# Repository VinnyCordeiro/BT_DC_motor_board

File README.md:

# BoxTurtle DC motors standalone board
A standalone board to control the DC motors of the BoxTurtle.

IMPORTANT NOTE: this design is still untested and being modified frequently as bugs/flaws are found. Do not order PCBs yet until we say it's safe!

## Why
The [AFC-Lite](https://github.com/xbst/AFC-Lite) is the preferred board for the BoxTurtle, but it is quite expensive and is only available on xbst's store (which is fair). However, many of us (myself included) already have a stash of old 3D printer controller boards to take care of the stepper motors, so only the DC motors were left without a standalone solution to control them. This board is an attempt to solve this situation.

I designed the board to be as easy and cheap as possible; with that in mind, here are the design constraints:
- All components/modules must be through hole mounted: I have professional training in electronics and the tools so SMD isn't a problem, but this isn't true for most of the hobbyists; by using through hole components the soldering complexity barrier is lowered;
- All modules are to be mounted on sockets: this opens some space on the board that would be otherwise unavailable. _DO NOT_ solder the modules directly on the board: not only you'll ruin the modularity of the design, you won't be able to install the power selection circuitry on the board (you may get away by soldering wires at the bottom side of the board for the switch, and solder the diodes at the bottom, but that's a bodge and shouldn't be used);
- I added as much useful information on the board silkscreen as I could, with the exception of the pinout. This should help guiding how the components/modules must be mounted, so it's on you if you let the magic smoke out if mounting them the other way around.

## Bill of Materials
This board was made with modularity in mind, so you'll need to buy those modules from Aliexpress (or any other source as long as the footprint matches; if they don't, you'll need to modify the PCB yourself):
|Component|No. Needed|Comment|Sourcing URL|
|---------|----------|-------|-------|
|5.08mm Screw Terminal|1|Power Input|https://www.lcsc.com/product-detail/Screw-span-style-background-color-ff0-terminal-span_MAX-MX129-5-08-02P-GN01-Cu-Y-A_C5188485.html|
|Automotive Mini-Blade Fuse Holder|1|Takes [Mini Automotive Fuses](https://www.keyelco.com/product.cfm/product_id/1376)|https://www.lcsc.com/product-detail/Fuse-Holders_XFCN-XF-506P_C492610.html|
|2A Mini Automotive fuse|1|For circuit safety|https://www.lcsc.com/product-detail/Automotive-Fuses_Littelfuse-0297002-WXNV_C151091.html|
|DC-DC 3A buck converter|1|Pick the 5V version|https://www.aliexpress.com/item/1005007031557776.html|
|LDO 800MA DC 5V to 3.3V buck converter|1|They come with right angle pin headers, you have to swap for straight pins|https://www.aliexpress.com/item/1005007792706354.html|
|DRV8837 2 Way DC H-Bridge|2|Pick the version with 2 drivers on the board|https://www.aliexpress.com/item/1005007587993921.html|
|SN65HVD230 CAN Network Transceiver Board|1|Optional, only if CAN bus will be used. You may need a jumper for the termination resistor if this is at the end of the CAN bus|https://www.aliexpress.com/item/1005006438437964.html|
|Jumper|1|If you doesn't have one|https://www.lcsc.com/product-detail/Shunts-Jumpers_TE-Connectivity-2-881545-2_C5166780.html|
|Pin socket 2 pins|4|For the 5V buck converter module|https://www.lcsc.com/product-detail/Female-Headers_BOOMELE-Boom-Precision-Elec-2-54-1-2P_C49661.html|
|Pin socket 3 pins|1|For the 3.3V buck converter module|https://www.lcsc.com/product-detail/Female-Headers_BOOMELE-Boom-Precision-Elec-2-54-1-3P_C146243.html|
|Pin socket 4 pins|1|For the CAN transceiver module|https://www.lcsc.com/product-detail/Female-Headers_BOOMELE-Boom-Precision-Elec-2-54-1-4P_C2718488.html|
|Pin socket 8 pins|4|For the DRV8837 modules|https://www.lcsc.com/product-detail/Female-Headers_BOOMELE-Boom-Precision-Elec-2-54-1-8P_C27438.html|
|Pin socket 20 pins|2|For the MCU|https://www.lcsc.com/product-detail/Female-Headers_Megastar-ZX-PM2-54-1-20PY_C7499336.html|
|JST XH 2 pins|4|To connect the DC motors|https://www.lcsc.com/product-detail/Wire-To-Board-Connector_JST-B2B-XH-A-LF-SN_C158012.html|
|JST XH 3 pins|12|To connect the endstops|https://www.lcsc.com/product-detail/Wire-To-Board-Connector_JST-B3B-XH-A-LF-SN_C144394.html|
|Schottky diode|2|You can reallistically use whatever through hole Schottky diode you have, even the BAT85 that used to be used on magnetic probes on old VORON releases|https://www.lcsc.com/product-detail/Schottky-Diodes_STMicroelectronics-BAT48_C283476.html|
|Switch|1|For selecting USB ou buck converter power|https://www.lcsc.com/product-detail/Slide-Switches_Korean-Hroparts-Elec-K3-1204D_C145861.html|
|Raspberry Pi Pico, or...|1|MCU (Pick one)|https://www.aliexpress.com/item/1005003708090298.html|
|Raspberry Pi Pico 2, or...|1|MCU (Pick one)|https://pt.aliexpress.com/item/1005005714757487.html|
|STM32F401 BlackPill|1|MCU (Pick one)|https://www.aliexpress.com/item/1005006127461676.html|

## Attributions
- Apex Mk2 Font Family by Jeremy Nelson, licensed under the 1001Fonts Free For Commercial Use License (FFC); obtained at https://www.1001fonts.com/apex-mk2-font.html
- Raspberry Pi Pico STEP file made by Raspberry Pi Foundation; obtained at https://datasheets.raspberrypi.com/pico/Pico-R3-step.zip
- Blackpill STM32F401CCU6 STEP model made by Adam Valent, published on GrabCAD by user Zawisza on August 22nd, 2022; obtained at https://grabcad.com/library/blackpill-stm32f401ccu6-1
- Mini Automotive fuse STEP model by Littelfuse, Inc.; obtained at https://www.littelfuse.com/products/fuses-overcurrent-protection/fuses/automotive-fuses/blade-fuses-shunt/mini/297/0297010-u
- K3-1204D 3D model made by Vinícius N. Cordeiro, using the datasheet as reference. The model isn't completely accurate as it's intended just as a mockup, but the only important feature missing are two 0.5 mm high bumps at the bottom of the switch. The PCB file is already accounting for that.

## Acknowledgements
- [Robert Klotz](https://github.com/ArmoredTurtle) for creating the amazing BoxTurtle project (I'm anxiously awaiting for the 8-Track!);
- [xbst](https://github.com/xbst) for designing the AFC-Lite. While the design files aren't available as I write, the schematics is public so I used them to create this board as well. Also, his mild distaste for the RP2040 MCUs on Klipper projects made me add support for a STM32 MCU board as well, which leads to;
- comradef191 and their [NyoomiesKME board](https://github.com/comradef191/NyoomiesKME) for the idea of adding support for both the Raspberry Pi Pico and the Black Pill STM32F401 MCU modules;
- Sanity Agathion on the [VORON Discord server](https://discord.gg/voron) for the tip that made me add the CAN bus module support;
- [timmit99](https://github.com/timmit99/) and [Shammy](https://xrbunker.works), both also from the VORON Discord server, for the support and also for providing a 3D model for the fuse holder (just catch the ball next time, Tim!);
- and [clee](https://github.com/clee): you know what you did.

## LICENSE
Copyright Vinícius N. Cordeiro 2025-2026

This source describes Open Hardware and is licensed under the CERN-OHL-S v2 or any later version.
You may redistribute and modify this source and make products using it under the terms of the CERN-OHL-S v2. (https://ohwr.org/cern_ohl_s_v2.txt)

This source is distributed WITHOUT ANY EXPRESS OR IMPLIED WARRANTY, INCLUDING OF MERCHANTABILITY, SATISFACTORY QUALITY AND FITNESS FOR A PARTICULAR PURPOSE. Please see the CERN-OHL-S v2 for applicable conditions.

Source Location: https://github.com/VinnyCordeiro/BT_DC_motor_board

As per CERN-OHL-S v2 section 4, should You produce hardware based on this source, You must where practicable maintain the Source Location visible on the PCB.

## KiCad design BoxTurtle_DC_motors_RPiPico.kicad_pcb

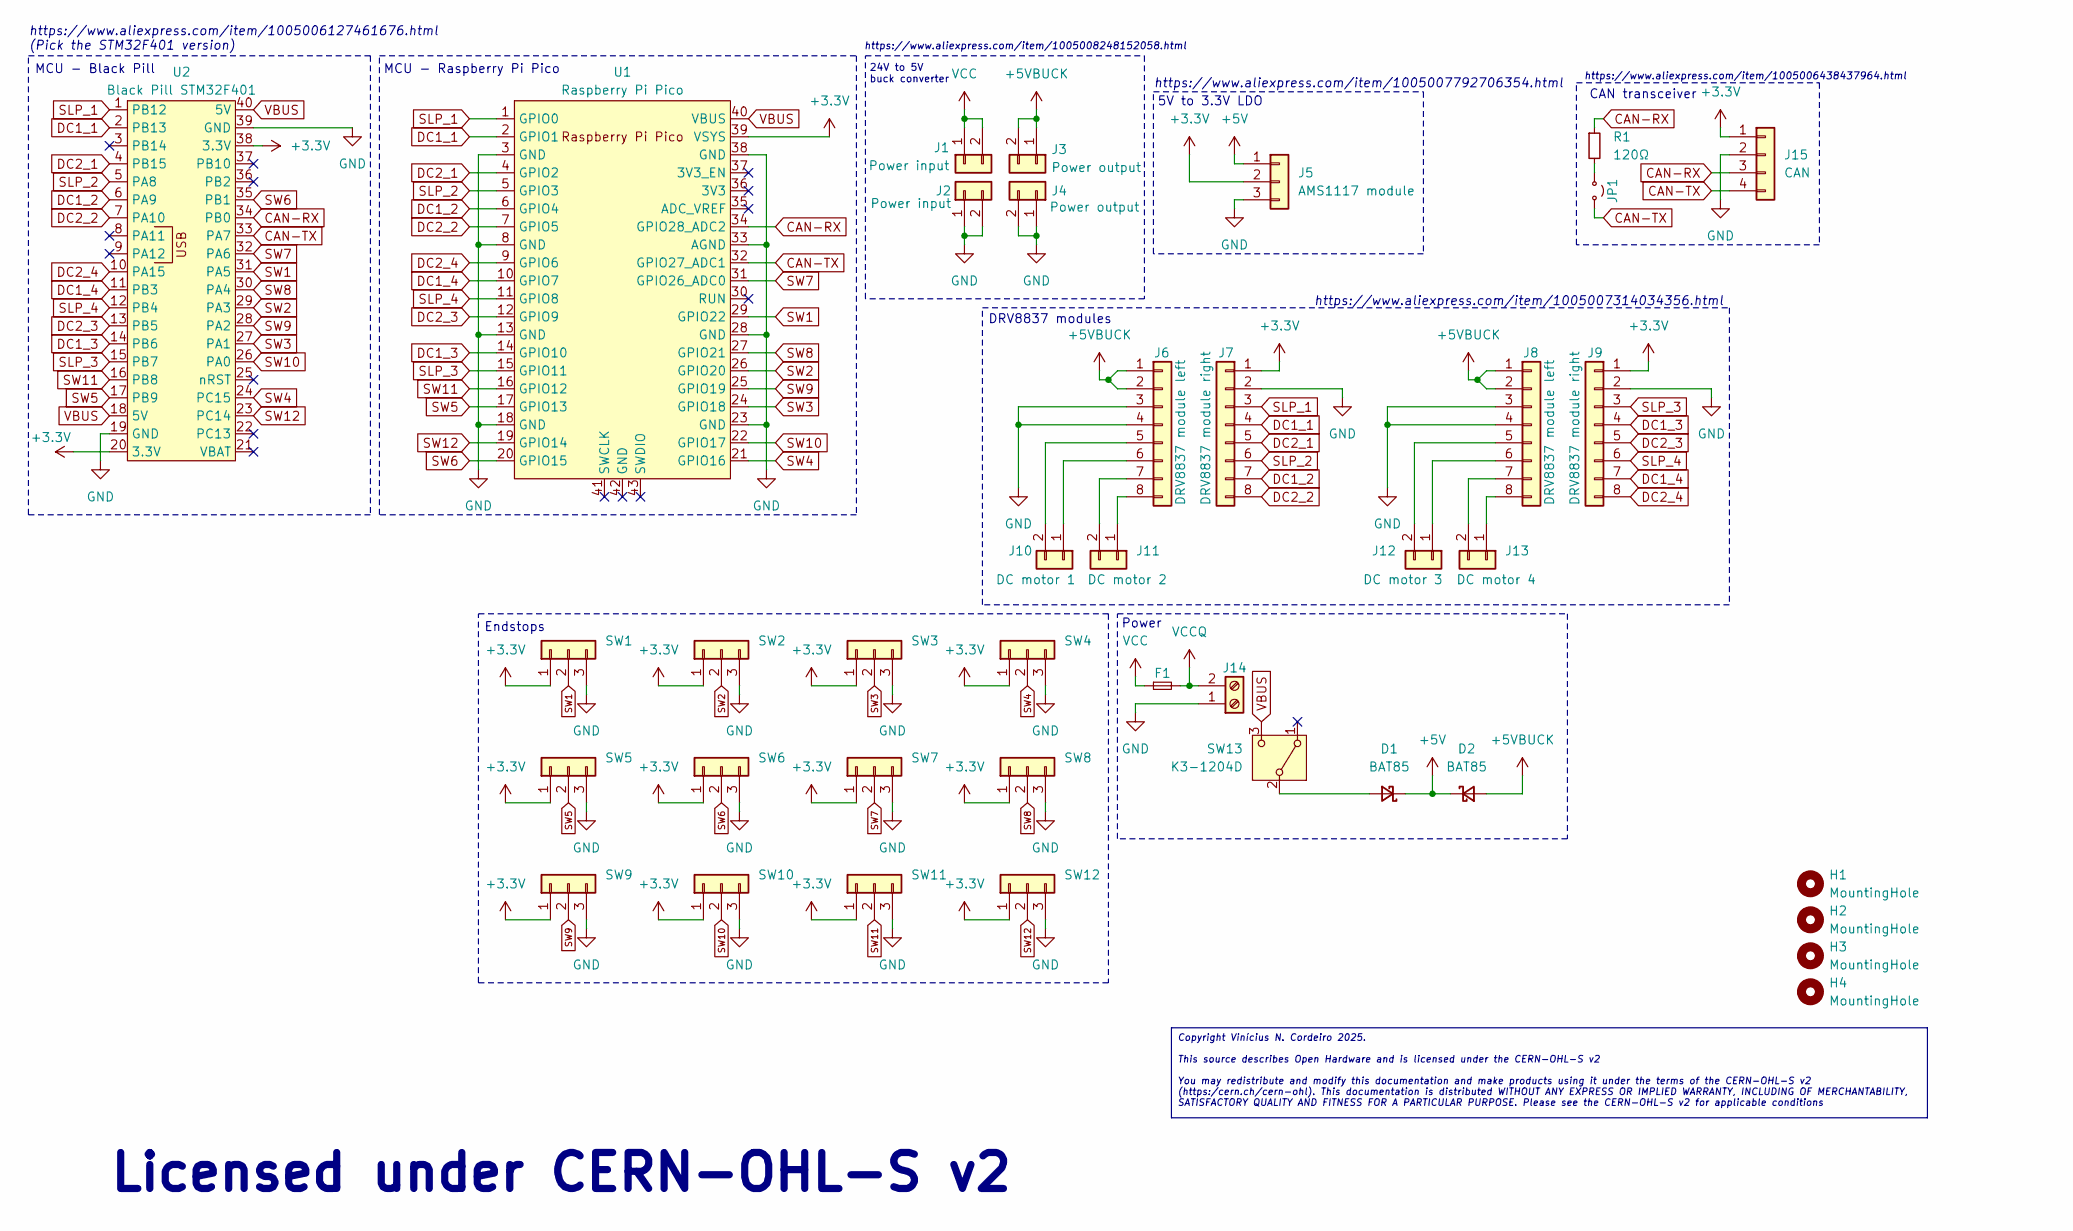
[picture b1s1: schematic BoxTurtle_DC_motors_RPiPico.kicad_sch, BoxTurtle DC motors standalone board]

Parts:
D1, D2: BAT85; D_DO-35_SOD27_P7.62mm_Horizontal
F1: Fuse_Small; XF-506P
H1, H2, H3, H4: MountingHole; MountingHole_3.2mm_M3
J1, J2: Power input; PinSocket_1x02_P2.54mm_Vertical
J3, J4: Power output; PinSocket_1x02_P2.54mm_Vertical
J5: AMS1117 module; PinSocket_1x03_P2.54mm_Vertical
J6, J8: DRV8837 module left; PinSocket_1x08_P2.54mm_Vertical
J7, J9: DRV8837 module right; PinSocket_1x08_P2.54mm_Vertical
J10: DC motor 1; JST_XH_B2B-XH-A_1x02_P2.50mm_Vertical
J11: DC motor 2; JST_XH_B2B-XH-A_1x02_P2.50mm_Vertical
J12: DC motor 3; JST_XH_B2B-XH-A_1x02_P2.50mm_Vertical
J13: DC motor 4; JST_XH_B2B-XH-A_1x02_P2.50mm_Vertical
J14: Screw_Terminal_01x02; TerminalBlock_Phoenix_MKDS-3-2-5.08_1x02_P5.08mm_Horizontal
J15: CAN; PinSocket_1x04_P2.54mm_Vertical
JP1: Jumper_2_Small_Open; PinHeader_1x02_P2.54mm_Vertical
R1: 120Ω; R_Axial_DIN0207_L6.3mm_D2.5mm_P10.16mm_Horizontal
SW1, SW2, SW3, SW4, SW5, SW6, SW7, SW8, SW9, SW10, SW11, SW12: Conn_01x03; JST_XH_B3B-XH-A_1x03_P2.50mm_Vertical
SW13: K3-1204D; LCSC C273395
U1: Raspberry Pi Pico; Pico
U2: Black Pill STM32F401; STM32F401 Black Pill

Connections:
+3.3V: J5.2, J7.1, J9.1, J15.1, SW1.1, SW2.1, SW3.1, SW4.1, SW5.1, SW6.1, SW7.1, SW8.1, SW9.1, SW10.1, SW11.1, SW12.1, U1.39 (VSYS), U2.20 (3.3V), U2.38 (3.3V)
+5V: D1.1 (K), D2.1 (K), J5.1
+5VBUCK: D2.2 (A), J3.1, J3.2, J6.1, J6.2, J8.1, J8.2
CAN-RX: J15.3, R1.1, U1.34 (GPIO28_ADC2), U2.34 (PB0)
CAN-TX: J15.4, JP1.2 (B), U1.32 (GPIO27_ADC1), U2.33 (PA7)
DC1_1: J7.4, U1.2 (GPIO1), U2.2 (PB13)
DC1_2: J7.7, U1.6 (GPIO4), U2.6 (PA9)
DC1_3: J9.4, U1.14 (GPIO10), U2.14 (PB6)
DC1_4: J9.7, U1.10 (GPIO7), U2.11 (PB3)
DC2_1: J7.5, U1.4 (GPIO2), U2.4 (PB15)
DC2_2: J7.8, U1.7 (GPIO5), U2.7 (PA10)
DC2_3: J9.5, U1.12 (GPIO9), U2.13 (PB5)
DC2_4: J9.8, U1.9 (GPIO6), U2.10 (PA15)
GND: J2.1, J2.2, J4.1, J4.2, J5.3, J6.3, J6.4, J7.2, J8.3, J8.4, J9.2, J14.1, J15.2, SW1.3, SW2.3, SW3.3, SW4.3, SW5.3, SW6.3, SW7.3, SW8.3, SW9.3, SW10.3, SW11.3, SW12.3, U1.3 (GND), U1.8 (GND), U1.13 (GND), U1.18 (GND), U1.23 (GND), U1.28 (GND), U1.33 (AGND), U1.38 (GND), U2.19 (GND), U2.39 (GND)
unnamed: D1.2 (A), SW13.2 (B)
unnamed: J6.6, J10.1
unnamed: J6.5, J10.2
unnamed: J6.8, J11.1
unnamed: J6.7, J11.2
unnamed: J8.6, J12.1
unnamed: J8.5, J12.2
unnamed: J8.8, J13.1
unnamed: J8.7, J13.2
unnamed: JP1.1 (A), R1.2
SLP_1: J7.3, U1.1 (GPIO0), U2.1 (PB12)
SLP_2: J7.6, U1.5 (GPIO3), U2.5 (PA8)
SLP_3: J9.3, U1.15 (GPIO11), U2.15 (PB7)
SLP_4: J9.6, U1.11 (GPIO8), U2.12 (PB4)
SW1: SW1.2, U1.29 (GPIO22), U2.31 (PA5)
SW2: SW2.2, U1.26 (GPIO20), U2.29 (PA3)
SW3: SW3.2, U1.24 (GPIO18), U2.27 (PA1)
SW4: SW4.2, U1.21 (GPIO16), U2.24 (PC15)
SW5: SW5.2, U1.17 (GPIO13), U2.17 (PB9)
SW6: SW6.2, U1.20 (GPIO15), U2.35 (PB1)
SW7: SW7.2, U1.31 (GPIO26_ADC0), U2.32 (PA6)
SW8: SW8.2, U1.27 (GPIO21), U2.30 (PA4)
SW9: SW9.2, U1.25 (GPIO19), U2.28 (PA2)
SW10: SW10.2, U1.22 (GPIO17), U2.26 (PA0)
SW11: SW11.2, U1.16 (GPIO12), U2.16 (PB8)
SW12: SW12.2, U1.19 (GPIO14), U2.23 (PC14)
VBUS: SW13.3 (C), U1.40 (VBUS), U2.18 (5V), U2.40 (5V)
VCC: F1.1, J1.1, J1.2
VCCQ: F1.2, J14.2

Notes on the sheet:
Copyright Vinícius N. Cordeiro 2025. This source describes Open Hardware and is licensed under the CERN-OHL-S v2 You may redistribute and modify this documentation and make products using it under the terms of the CERN-OHL-S v2 (https:/cern.ch/cern-ohl). This documentation is distributed WITHOUT AN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
CAN transceiver
MCU - Raspberry Pi Pico
https://www.aliexpress.com/item/1005006127461676.html (Pick the STM32F401 version)
Licensed under CERN-OHL-S v2
https://www.aliexpress.com/item/1005006438437964.html
5V to 3.3V LDO
https://www.aliexpress.com/item/1005007792706354.html
MCU - Black Pill
https://www.aliexpress.com/item/1005008248152058.html
Endstops
24V to 5V buck converter
DRV8837 modules
https://www.aliexpress.com/item/1005007314034356.html
Power

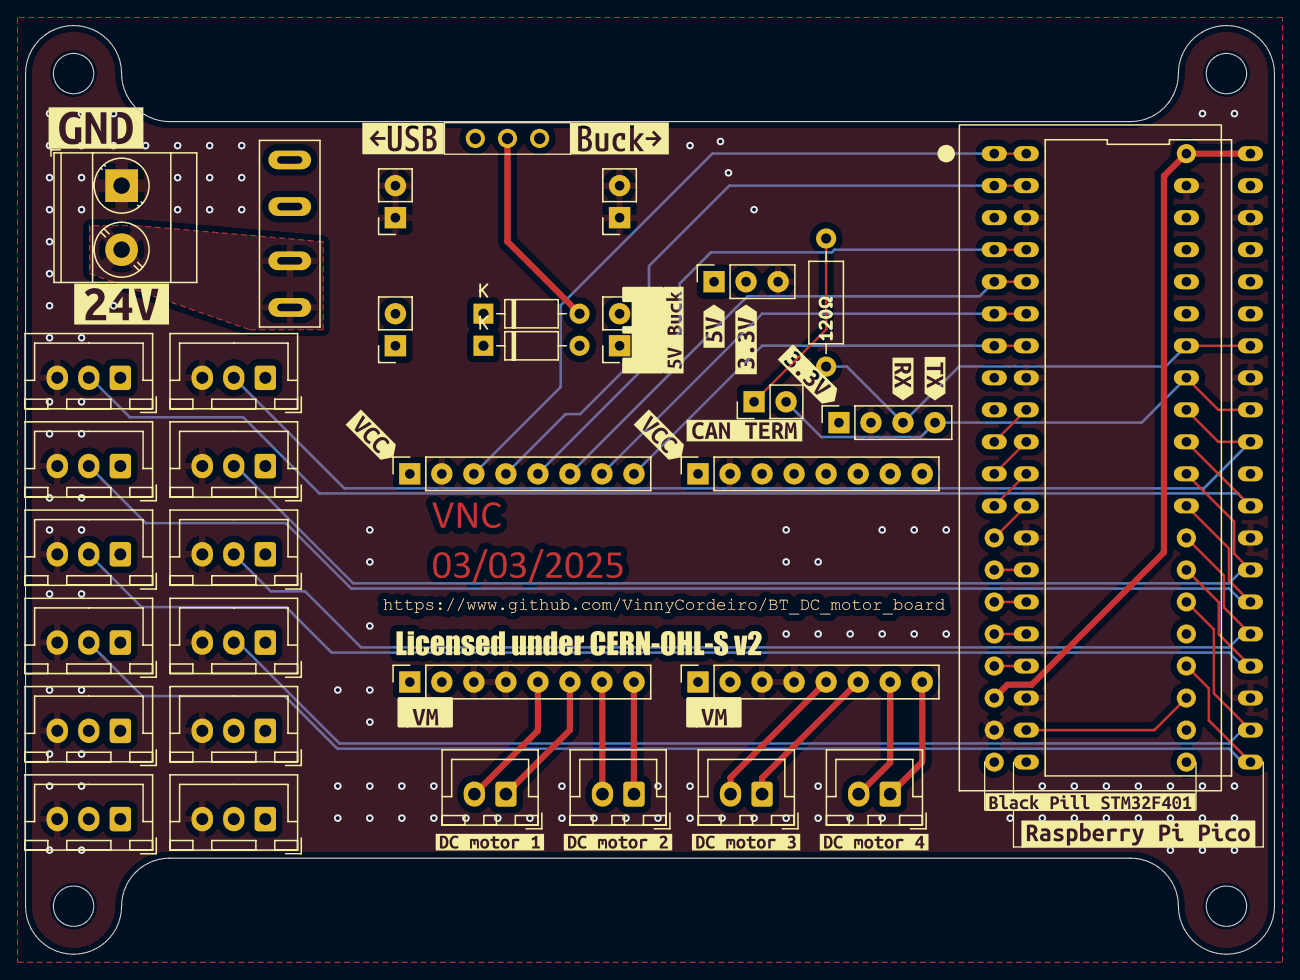
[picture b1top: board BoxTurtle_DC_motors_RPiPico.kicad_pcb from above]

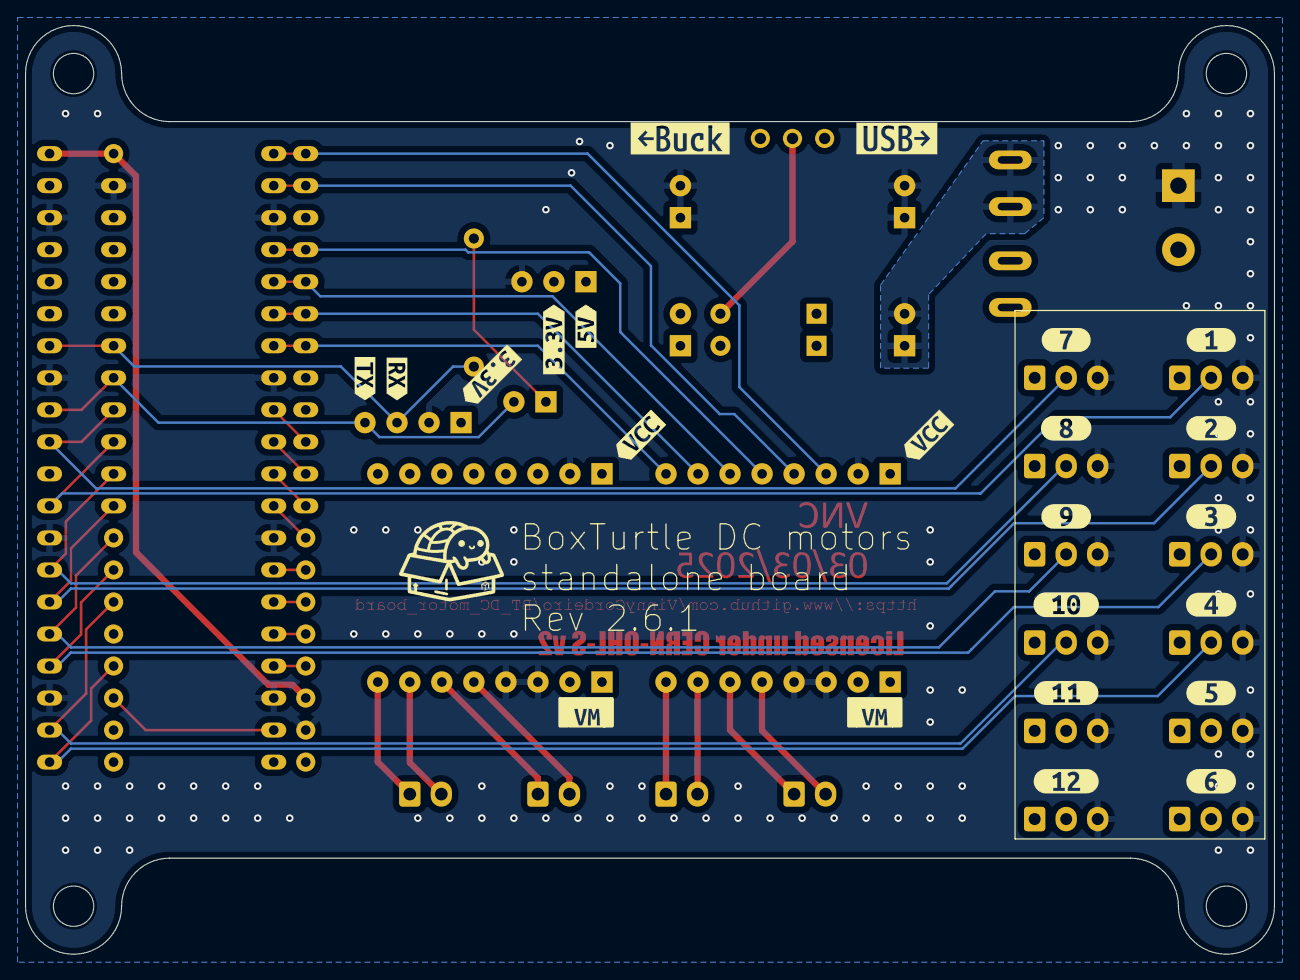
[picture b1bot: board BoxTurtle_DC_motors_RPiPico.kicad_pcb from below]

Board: 4 copper layers, 99.1 x 73.7 mm, 83 parts (23 on the bottom side), 43 nets.

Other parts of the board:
kibuzzard-67A0CA07: G***; kibuzzard-67A0CA07
kibuzzard-67A0043B: G***; kibuzzard-67A0043B
kibuzzard-67A00413: G***; kibuzzard-67A00413
kibuzzard-67C5FAD7: G***; kibuzzard-67C5FAD7
kibuzzard-67C5FB16: G***; kibuzzard-67C5FB16
kibuzzard-67C5FB88: G***; kibuzzard-67C5FB88
kibuzzard-67C5FBBE: G***; kibuzzard-67C5FBBE
kibuzzard-67C627D9: G***; kibuzzard-67C627D9
kibuzzard-67C627E2: G***; kibuzzard-67C627E2
kibuzzard-67C627EC: G***; kibuzzard-67C627EC
kibuzzard-67C627F5: G***; kibuzzard-67C627F5
kibuzzard-67C628B6: G***; kibuzzard-67C628B6
kibuzzard-67C628BD: G***; kibuzzard-67C628BD
kibuzzard-67C6285C: G***; kibuzzard-67C6285C
kibuzzard-67C6289C: G***; kibuzzard-67C6289C
kibuzzard-679EE0D3: G***; kibuzzard-679EE0D3
kibuzzard-679EE0F2: G***; kibuzzard-679EE0F2
kibuzzard-679EE1A8: G***; kibuzzard-679EE1A8
kibuzzard-679EE1B2: G***; kibuzzard-679EE1B2
kibuzzard-679EE6D0: G***; kibuzzard-679EE6D0
kibuzzard-679EE6DA: G***; kibuzzard-679EE6DA
kibuzzard-679EE6E6: G***; kibuzzard-679EE6E6
kibuzzard-679EE19C: G***; kibuzzard-679EE19C
kibuzzard-679EE64B: G***; kibuzzard-679EE64B
kibuzzard-679EE68A: G***; kibuzzard-679EE68A
kibuzzard-679EE72D: G***; kibuzzard-679EE72D
kibuzzard-679EE78C: G***; kibuzzard-679EE78C
kibuzzard-679EE189: G***; kibuzzard-679EE189
kibuzzard-679EE681: G***; kibuzzard-679EE681
kibuzzard-679EE693: G***; kibuzzard-679EE693
kibuzzard-679EE762: G***; kibuzzard-679EE762
kibuzzard-679EE772: G***; kibuzzard-679EE772
kibuzzard-679EE781: G***; kibuzzard-679EE781
kibuzzard-679EE822, kibuzzard-679EE822#2, kibuzzard-679EE822#3, kibuzzard-679EE822#4: G***; kibuzzard-679EE822
kibuzzard-679EE836, kibuzzard-679EE836#2: G***; kibuzzard-679EE836
kibuzzard-679FA142, kibuzzard-679FA142#2: G***; kibuzzard-679FA142
kibuzzard-679FA150, kibuzzard-679FA150#2: G***; kibuzzard-679FA150
kibuzzard-679FB212: G***; kibuzzard-679FB212

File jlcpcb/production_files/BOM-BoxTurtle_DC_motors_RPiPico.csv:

Comment,Designator,Footprint,LCSC,Quantity
K3-1204D,SW13,K3-1204D,C145861,1
DRV8837 module right,J7,PinSocket_1x08_P2.54mm_Vertical,,1
Conn_01x03,SW7,JST_XH_B3B-XH-A_1x03_P2.50mm_Vertical,,1
AMS1117 module,J5,PinSocket_1x03_P2.54mm_Vertical,,1
Conn_01x03,SW2,JST_XH_B3B-XH-A_1x03_P2.50mm_Vertical,,1
Conn_01x03,SW8,JST_XH_B3B-XH-A_1x03_P2.50mm_Vertical,,1
DC motor 1,J10,JST_XH_B2B-XH-A_1x02_P2.50mm_Vertical,,1
Conn_01x03,SW1,JST_XH_B3B-XH-A_1x03_P2.50mm_Vertical,,1
DC motor 2,J11,JST_XH_B2B-XH-A_1x02_P2.50mm_Vertical,,1
DRV8837 module right,J9,PinSocket_1x08_P2.54mm_Vertical,,1
Conn_01x03,SW6,JST_XH_B3B-XH-A_1x03_P2.50mm_Vertical,,1
Power input,J2,PinSocket_1x02_P2.54mm_Vertical,,1
Conn_01x03,SW4,JST_XH_B3B-XH-A_1x03_P2.50mm_Vertical,,1
Conn_01x03,SW5,JST_XH_B3B-XH-A_1x03_P2.50mm_Vertical,,1
Power output,J3,PinSocket_1x02_P2.54mm_Vertical,,1
DRV8837 module left,J6,PinSocket_1x08_P2.54mm_Vertical,,1
DRV8837 module left,J8,PinSocket_1x08_P2.54mm_Vertical,,1
Raspberry Pi Pico,U1,Pico,,1
Conn_01x03,SW11,JST_XH_B3B-XH-A_1x03_P2.50mm_Vertical,,1
DC motor 4,J13,JST_XH_B2B-XH-A_1x02_P2.50mm_Vertical,,1
DC motor 3,J12,JST_XH_B2B-XH-A_1x02_P2.50mm_Vertical,,1
Conn_01x03,SW10,JST_XH_B3B-XH-A_1x03_P2.50mm_Vertical,,1
Power input,J1,PinSocket_1x02_P2.54mm_Vertical,,1
Conn_01x03,SW9,JST_XH_B3B-XH-A_1x03_P2.50mm_Vertical,,1
Conn_01x03,SW12,JST_XH_B3B-XH-A_1x03_P2.50mm_Vertical,,1
Conn_01x03,SW3,JST_XH_B3B-XH-A_1x03_P2.50mm_Vertical,,1
Power output,J4,PinSocket_1x02_P2.54mm_Vertical,,1
Screw_Terminal_01x02,J14,TerminalBlock_Phoenix_MKDS-3-2-5.08_1x02_P5.08mm_Horizontal,,1
120Ω,R1,R_Axial_DIN0207_L6.3mm_D2.5mm_P10.16mm_Horizontal,,1
Jumper_2_Small_Open,JP1,PinHeader_1x02_P2.54mm_Vertical,,1
CAN,J15,PinSocket_1x04_P2.54mm_Vertical,,1
BAT85,D2,D_DO-35_SOD27_P7.62mm_Horizontal,,1
BAT85,D1,D_DO-35_SOD27_P7.62mm_Horizontal,,1
Black Pill STM32F401,U2,STM32F401 Black Pill,,1
Fuse_Small,F1,XF-506P,,1

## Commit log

2025-02-03 Initial release
2025-02-03 Update README.md
    There's always a typo to correct after you publish, even if you spend over half an hour revising it...
2025-02-03 Fuse & Gerber
    Added the fuse for safety, also uploaded Gerber files for those who want to make their own board.
2025-02-03 Update CHANGES.md
    The bullets for unordered lists were gone for whatever reason, re-adding them.
2025-02-03 Added fuse holder 3D model part 1
    Changes for the PCB file and README.md; also included a render of the board that will be inserted on the README.md later.
2025-02-03 Added fuse holder 3D model part 2
    The fuse holder 3D model itself.
2025-02-03 Update README.md
    Added the inner marking to display the board's render.
2025-02-03 Update README.md
    Another typo found...
2025-02-03 Added PINOUT.md
2025-02-03 Update PINOUT.md
    Tables not rendering
2025-02-03 Update PINOUT.md
    Tables not rendering, part 2...
2025-02-03 Update PINOUT.md
    Tables not rendering, part 3. Third time is the charm anyway...
2025-02-03 Update PINOUT.md
    FOUR changes to find the typos, unbelievable...
2025-02-03 Update PINOUT.md
    Actually it needed five...
2025-02-03 Corrected 5V source for DC motors
    As it was this board will blow your USB port.
2025-02-03 Correct fatal flaw on 5V supply for DC motors
2025-02-04 Initial release of config file
    This should be added at the config/mcu directory of the AFC Klipper add-on. Subject to testing.
2025-02-05 Update README.md
    Corrected info about the fuse
2025-02-05 Update CHANGES.md
    Corrected info about the fuse
2025-02-05 Updated PCB
    Modified some more silkscreens, added a fuse 3D model
2025-02-05 Fuse 3D model
    Downloaded from Littelfuse website
2025-02-22 Update README.md
    Added Copyright notice, fixed some grammar errors.
2025-02-22 Update PINOUT.md
    Changed SW6 from PC13 to PB1 on the Black Pill because that pin is shared with the LED and that could lead to strange behavior.
2025-02-22 Revision 2.4 - QoL updates
    Increased CAN bus resistor footprint; reduced hole diameter on Raspberry Pi Pico's socket pads for snugger fit; changed pin for SW6 on the Black Pill.
2025-02-22 Update BT_DC_PCB.cfg
    SW6 on the Black Pill is now on PB1
2025-02-22 Update TODO.md
    Typo
2025-02-22 Update README.md
    Typo
2025-02-22 Update README.md
    Changed fuse to 5A, the previous one was excessively high current.
2025-02-25 Revision 2.5
    Corrected the footprint for the 24V to 5V buck converter and the DRV8837 modules.
2025-02-26 Update README.md
    Added a source for the Raspberry Pi Pico 2 (actually a clone using USB Type C receptacle because we are in 2025), corrected a typo.
2025-02-26 Rev. 2.5 Gerber files
    Forgot to upload earlier...
2025-03-03 Update README.md
    Changed the fuse again, changed the switch as the old one is too big for the footprint changes that are needed.
2025-03-03 Revision 2.6
    Updated footprints again now that I have them on hand to accurately make measures, changed selection switch for a model that is smaller and carry more current.
2025-03-03 Revision 2.6 Gerber files
2025-03-03 Updated render picture for Rev. 2.6
2025-03-04 Revision 2.6.1
    Just silkscreen changes
2025-03-04 Revision 2.6.1
    Minor silkscreen markings adjustments.
2025-03-04 Update README.md
    Added the JST XH connectors
2026-04-26 Revision 2.6.2
    1. adjusted sockets for buck converter; 2. adjusted endstops to follow same pattern as AFC Lite
2026-04-26 Revision 2.6.2 - DRC errors correction
    Had to correct them to generate the Gerber files.
2026-04-26 Revision 2.6.2 - Gerber & production files
2026-04-26 Updated README.md
    Fucking AVAST thinks a text file is infected with a worm...
2026-05-02 Revision 2.6.3
    Added a solder jumper for powering the microcontroller board while using CANbus; updated silkscreen.
2026-05-02 Revision 2.6.3 - Gerber & production files
2026-05-03 Update README.md
    Excluded the line in the BOM with the 120 ohms resistor, it's already included on the CAN transceiver board.
2026-05-03 Revision 2.6.4
    Will update the Gerber files later
2026-05-03 Revision 2.6.4 - Gerber & production files
2026-05-03 Update README.md
    Forgot to delete a line in the BOM: the pin header for the 120 ohms resistor that now isn't there anymore.
2026-05-03 Updated render image
2026-05-03 Update README.md
    Dead link for the Raspberry Pi Pico 2 corrected
